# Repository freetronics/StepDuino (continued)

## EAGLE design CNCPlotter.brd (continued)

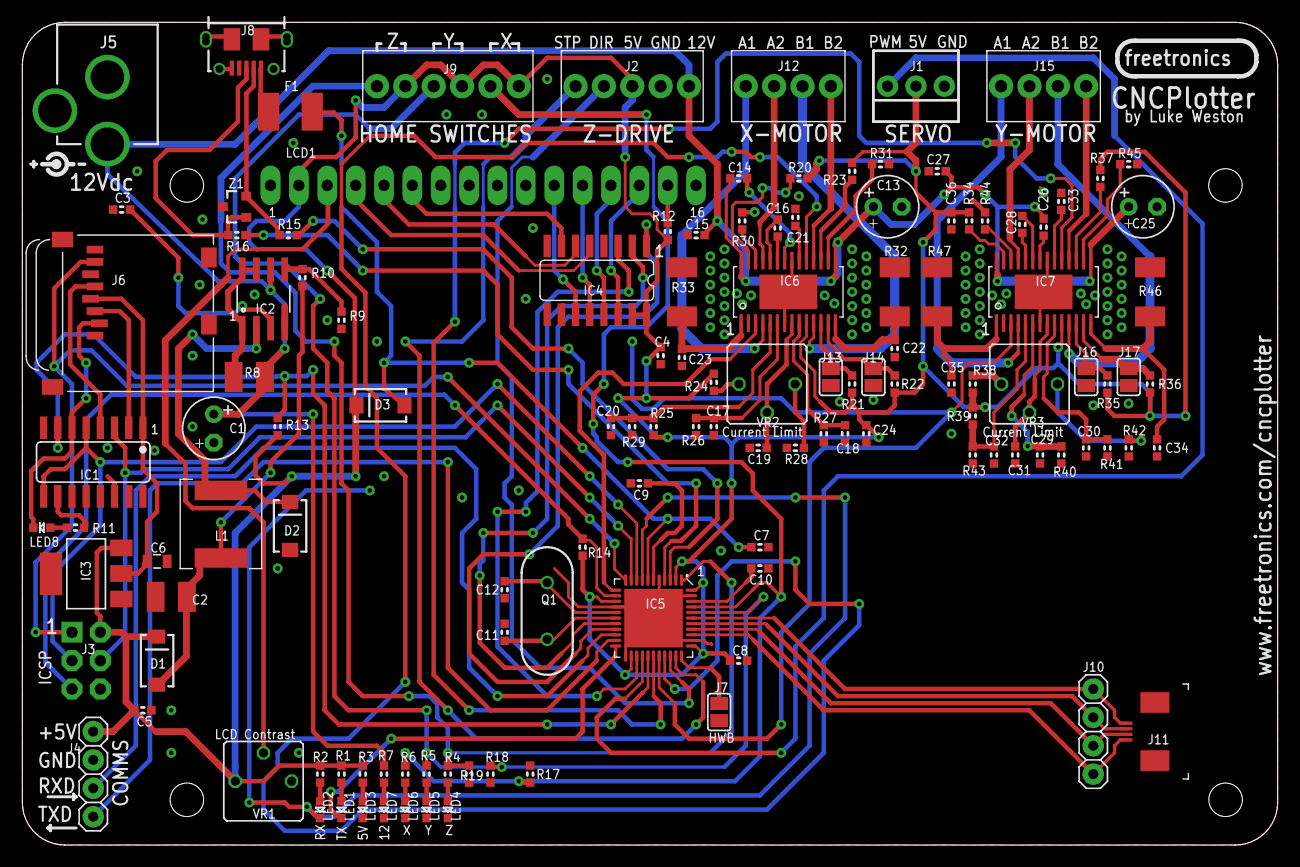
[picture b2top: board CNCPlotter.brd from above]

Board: 2 copper layers, 112.4 x 73.7 mm, 126 parts (0 on the bottom side), 111 nets.

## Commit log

2013-04-08 Removed CNCPlotter files
2013-04-08 Renamed project files
2013-04-08 Start of major restructure using ATmega328
2013-08-05 Routing for v1.0 release
2014-02-19 Added documentation and preview image
2014-11-05 Made 0603 resistor and capacitor footprints consistent
2014-11-06 Add PDF schematic
